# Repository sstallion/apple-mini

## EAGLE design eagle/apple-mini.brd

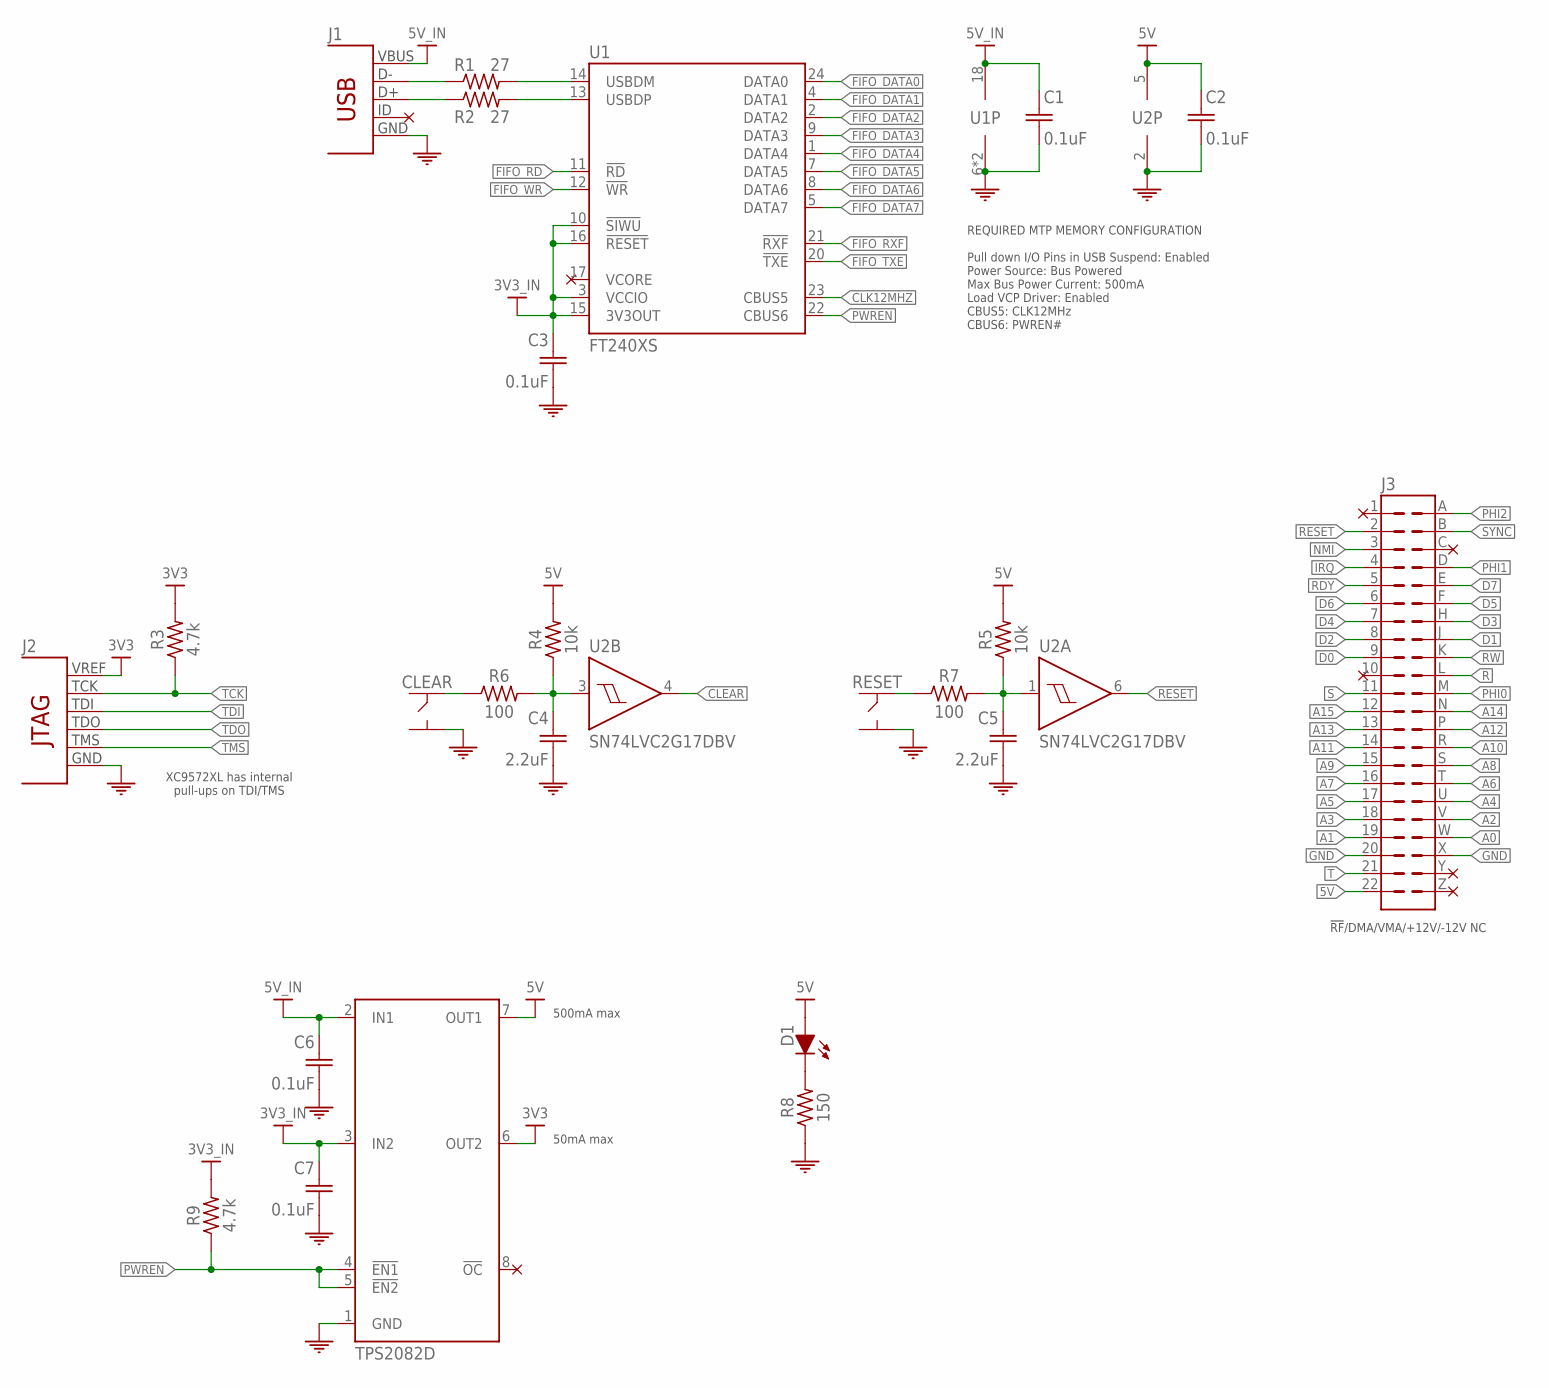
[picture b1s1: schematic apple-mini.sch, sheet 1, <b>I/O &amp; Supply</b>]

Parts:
C1, C2, C3, C6, C7: 0.1uF; 0603; MFR_PARTNO C0603C104K4RACTU
C4, C5: 2.2uF; 0603; MFR_PARTNO C0603C225K4PACTU
CLEAR: TACTSW; SMTR92
D1: CHIPLED; 0603; MFR_PARTNO LTST-C190KGKT
J1: USBMICRO; 10118193-0001LF
J2: JTAG; PH07-2-SMT
J3: RBM22DRTN; M22DRTN
R1, R2: 27; 0402; MFR_PARTNO RC0402JR-0727RL
R3, R9: 4.7k; 0603; MFR_PARTNO RC0603JR-074K7L
R4, R5: 10k; 0603; MFR_PARTNO RC0603JR-0710KL
R6, R7: 100; 0603; MFR_PARTNO ESR03EZPJ101
R8: 150; 0603; MFR_PARTNO ESR03EZPJ181
RESET: TACTSW; SMTR92
U1: FT240XS; SSOP24
U2: SN74LVC2G17DBV; SOT23-6
U3: TPS2082D; SOIC8

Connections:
3V3: J2.2 (VREF), R3.2, U3.6 (OUT2); also elsewhere on the board
3V3_IN: C3.1, C7.1, R9.2, U1.3 (VCCIO), U1.10 (!SIWU), U1.15 (3V3OUT), U1.16 (!RESET), U3.3 (IN2)
5V: C2.1, D1.2, J3.22, R4.2, R5.2, U2.5 (VCC), U3.7 (OUT1); also elsewhere on the board
5V_IN: C1.1, C6.1, J1.1, U1.18 (VCC), U3.2 (IN1)
A0: J3.W; also elsewhere on the board
A1: J3.19; also elsewhere on the board
A2: J3.V; also elsewhere on the board
A3: J3.18; also elsewhere on the board
A4: J3.U; also elsewhere on the board
A5: J3.17; also elsewhere on the board
A6: J3.T; also elsewhere on the board
A7: J3.16; also elsewhere on the board
A8: J3.S; also elsewhere on the board
A9: J3.15; also elsewhere on the board
A10: J3.R; also elsewhere on the board
A11: J3.14; also elsewhere on the board
A12: J3.P; also elsewhere on the board
A13: J3.13; also elsewhere on the board
A14: J3.N; also elsewhere on the board
A15: J3.12; also elsewhere on the board
CLEAR: U2.4 (Y); also elsewhere on the board
CLK12MHZ: U1.23 (CBUS5); also elsewhere on the board
D0: J3.9; also elsewhere on the board
D1: J3.J; also elsewhere on the board
D2: J3.8; also elsewhere on the board
D3: J3.H; also elsewhere on the board
D4: J3.7; also elsewhere on the board
D5: J3.F; also elsewhere on the board
D6: J3.6; also elsewhere on the board
D7: J3.E; also elsewhere on the board
FIFO_DATA0: U1.24 (DATA0); also elsewhere on the board
FIFO_DATA1: U1.4 (DATA1); also elsewhere on the board
FIFO_DATA2: U1.2 (DATA2); also elsewhere on the board
FIFO_DATA3: U1.9 (DATA3); also elsewhere on the board
FIFO_DATA4: U1.1 (DATA4); also elsewhere on the board
FIFO_DATA5: U1.7 (DATA5); also elsewhere on the board
FIFO_DATA6: U1.8 (DATA6); also elsewhere on the board
FIFO_DATA7: U1.5 (DATA7); also elsewhere on the board
FIFO_RD: U1.11 (!RD); also elsewhere on the board
FIFO_RXF: U1.21 (!RXF); also elsewhere on the board
FIFO_TXE: U1.20 (!TXE); also elsewhere on the board
FIFO_WR: U1.12 (!WR); also elsewhere on the board
GND: C1.2, C2.2, C3.2, C4.2, C5.2, C6.2, C7.2, CLEAR.3 (2), CLEAR.4 (2), J1.5, J1.6 (5), J1.7 (5), J1.8 (5), J1.9 (5), J2.3 (GND), J2.5 (GND), J2.7 (GND), J2.9 (GND), J2.11 (GND), J3.20, J3.X, R8.1, RESET.3 (2), RESET.4 (2), U1.6 (GND), U1.19 (GND), U2.2 (GND), U3.1 (GND); also elsewhere on the board
IRQ: J3.4; also elsewhere on the board
unnamed: D1.1, R8.2
unnamed: J1.2, R1.1
unnamed: J1.3, R2.1
unnamed: CLEAR.1, CLEAR.2 (1), R6.1
unnamed: R1.2, U1.14 (USBDM)
unnamed: R2.2, U1.13 (USBDP)
unnamed: R7.1, RESET.1, RESET.2 (1)
unnamed: C4.1, R4.1, R6.2, U2.3 (A)
unnamed: C5.1, R5.1, R7.2, U2.1 (A)
NMI: J3.3; also elsewhere on the board
PHI0: J3.M; also elsewhere on the board
PHI1: J3.D; also elsewhere on the board
PHI2: J3.A; also elsewhere on the board
PWREN: R9.1, U1.22 (CBUS6), U3.4 (!EN1), U3.5 (!EN2)
R: J3.L; also elsewhere on the board
RDY: J3.5; also elsewhere on the board
RESET: J3.2, U2.6 (Y); also elsewhere on the board
RW: J3.K; also elsewhere on the board
S: J3.11; also elsewhere on the board
SYNC: J3.B; also elsewhere on the board
T: J3.21; also elsewhere on the board
TCK: J2.6 (TCK), R3.1; also elsewhere on the board
TDI: J2.10 (TDI); also elsewhere on the board
TDO: J2.8 (TDO); also elsewhere on the board
TMS: J2.4 (TMS); also elsewhere on the board
VCORE: U1.17 (VCORE)

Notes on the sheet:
XC9572XL has internal pull-ups on TDI/TMS
!RF!/DMA/VMA/+12V/-12V NC
REQUIRED MTP MEMORY CONFIGURATION Pull down I/O Pins in USB Suspend: Enabled Power Source: Bus Powered Max Bus Power Current: 500mA Load VCP Driver: Enabled CBUS5: CLK12MHz CBUS6: PWREN#
50mA max
500mA max

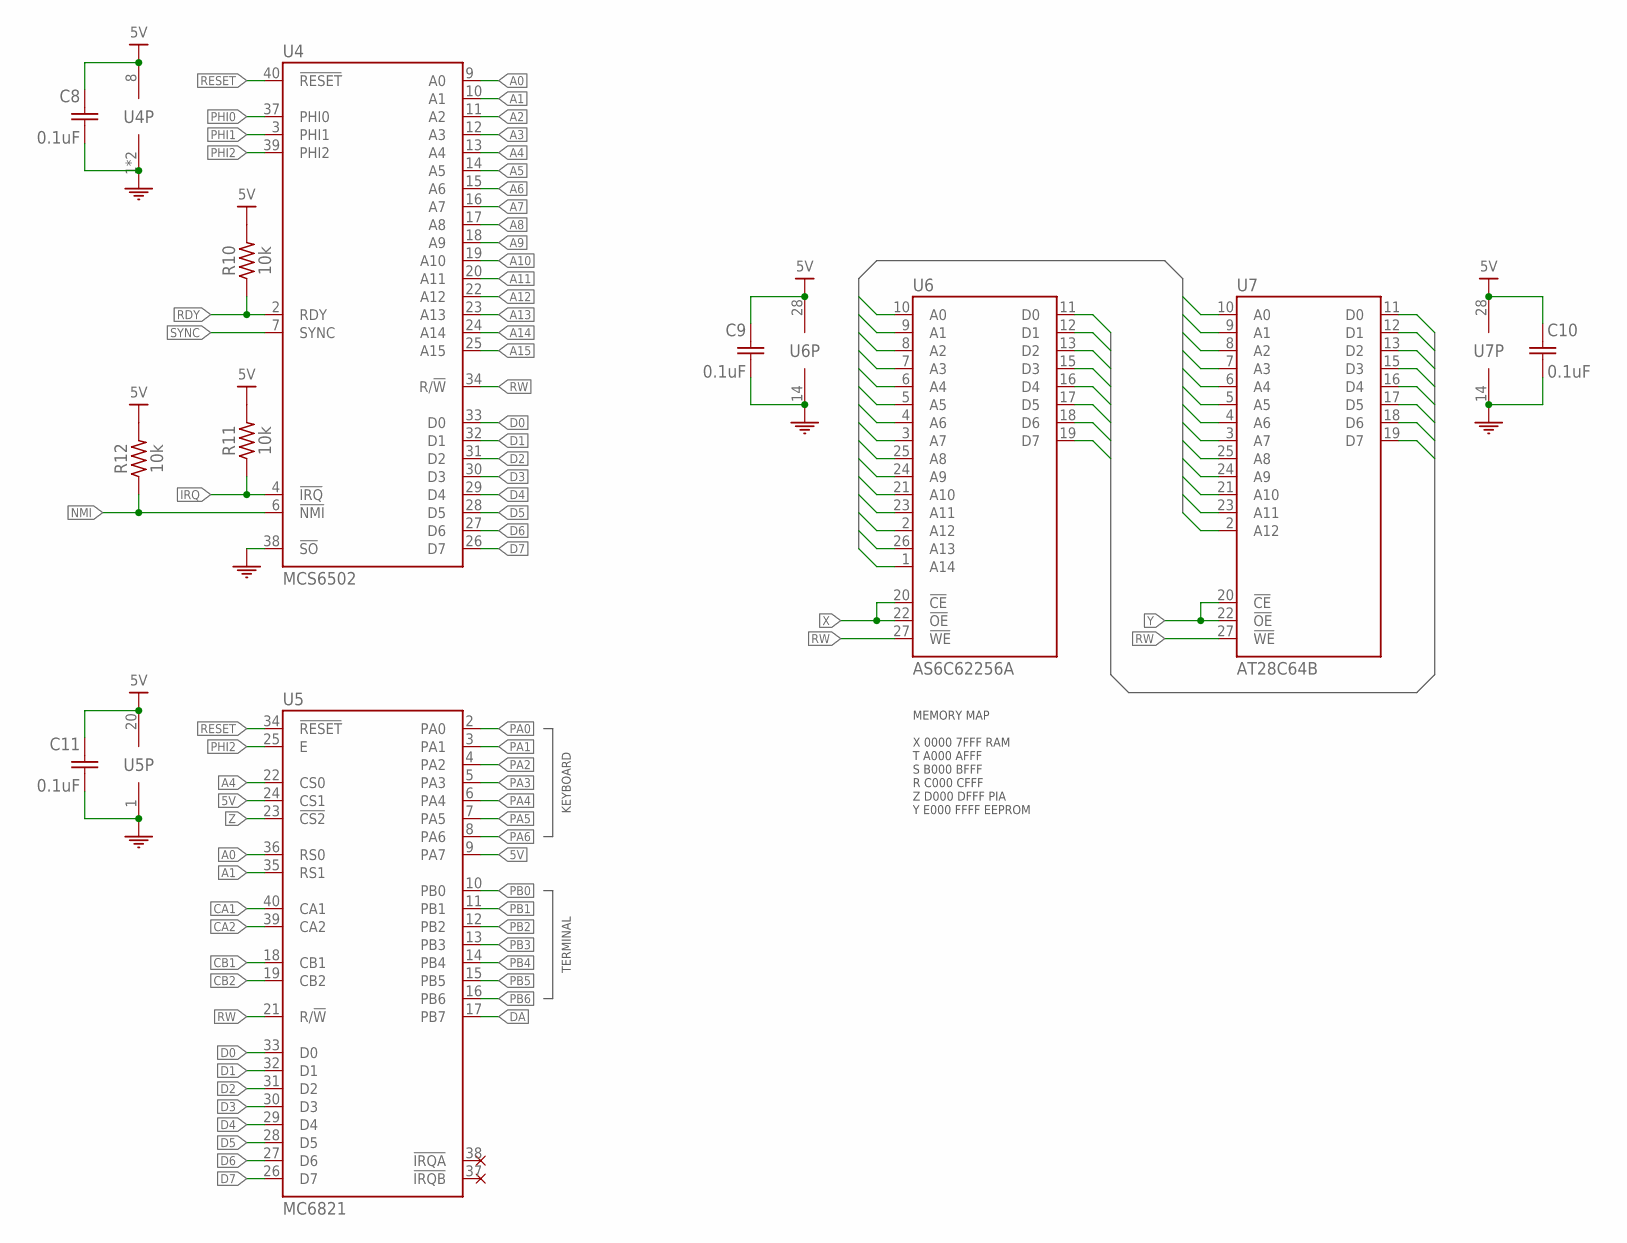
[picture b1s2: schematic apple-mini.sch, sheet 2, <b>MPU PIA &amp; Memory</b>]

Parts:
C8, C9, C10, C11: 0.1uF; 0603; MFR_PARTNO C0603C104K4RACTU
R10, R11, R12: 10k; 0603; MFR_PARTNO RC0603JR-0710KL
U4: MCS6502; DIP40
U5: MC6821; DIP40
U6: AS6C62256A; DIP28
U7: AT28C64B; DIP28

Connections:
5V: C8.1, C9.1, C10.1, C11.1, R10.2, R11.2, R12.2, U4.8 (VCC), U5.9 (PA7), U5.20 (VCC), U5.24 (CS1), U6.28 (VCC), U7.28 (VCC); also elsewhere on the board
A0: U4.9 (A0), U5.36 (RS0), U6.10 (A0), U7.10 (A0); also elsewhere on the board
A1: U4.10 (A1), U5.35 (RS1), U6.9 (A1), U7.9 (A1); also elsewhere on the board
A2: U4.11 (A2), U6.8 (A2), U7.8 (A2); also elsewhere on the board
A3: U4.12 (A3), U6.7 (A3), U7.7 (A3); also elsewhere on the board
A4: U4.13 (A4), U5.22 (CS0), U6.6 (A4), U7.6 (A4); also elsewhere on the board
A5: U4.14 (A5), U6.5 (A5), U7.5 (A5); also elsewhere on the board
A6: U4.15 (A6), U6.4 (A6), U7.4 (A6); also elsewhere on the board
A7: U4.16 (A7), U6.3 (A7), U7.3 (A7); also elsewhere on the board
A8: U4.17 (A8), U6.25 (A8), U7.25 (A8); also elsewhere on the board
A9: U4.18 (A9), U6.24 (A9), U7.24 (A9); also elsewhere on the board
A10: U4.19 (A10), U6.21 (A10), U7.21 (A10); also elsewhere on the board
A11: U4.20 (A11), U6.23 (A11), U7.23 (A11); also elsewhere on the board
A12: U4.22 (A12), U6.2 (A12), U7.2 (A12); also elsewhere on the board
A13: U4.23 (A13), U6.26 (A13); also elsewhere on the board
A14: U4.24 (A14), U6.1 (A14); also elsewhere on the board
A15: U4.25 (A15); also elsewhere on the board
CA1: U5.40 (CA1); also elsewhere on the board
CA2: U5.39 (CA2); also elsewhere on the board
CB1: U5.18 (CB1); also elsewhere on the board
CB2: U5.19 (CB2); also elsewhere on the board
D0: U4.33 (D0), U5.33 (D0), U6.11 (D0), U7.11 (D0); also elsewhere on the board
D1: U4.32 (D1), U5.32 (D1), U6.12 (D1), U7.12 (D1); also elsewhere on the board
D2: U4.31 (D2), U5.31 (D2), U6.13 (D2), U7.13 (D2); also elsewhere on the board
D3: U4.30 (D3), U5.30 (D3), U6.15 (D3), U7.15 (D3); also elsewhere on the board
D4: U4.29 (D4), U5.29 (D4), U6.16 (D4), U7.16 (D4); also elsewhere on the board
D5: U4.28 (D5), U5.28 (D5), U6.17 (D5), U7.17 (D5); also elsewhere on the board
D6: U4.27 (D6), U5.27 (D6), U6.18 (D6), U7.18 (D6); also elsewhere on the board
D7: U4.26 (D7), U5.26 (D7), U6.19 (D7), U7.19 (D7); also elsewhere on the board
DA: U5.17 (PB7); also elsewhere on the board
GND: C8.2, C9.2, C10.2, C11.2, U4.1 (GND), U4.21 (GND), U4.38 (!SO), U5.1 (GND), U6.14 (GND), U7.14 (GND); also elsewhere on the board
IRQ: R11.1, U4.4 (!IRQ); also elsewhere on the board
NMI: R12.1, U4.6 (!NMI); also elsewhere on the board
PA0: U5.2 (PA0); also elsewhere on the board
PA1: U5.3 (PA1); also elsewhere on the board
PA2: U5.4 (PA2); also elsewhere on the board
PA3: U5.5 (PA3); also elsewhere on the board
PA4: U5.6 (PA4); also elsewhere on the board
PA5: U5.7 (PA5); also elsewhere on the board
PA6: U5.8 (PA6); also elsewhere on the board
PB0: U5.10 (PB0); also elsewhere on the board
PB1: U5.11 (PB1); also elsewhere on the board
PB2: U5.12 (PB2); also elsewhere on the board
PB3: U5.13 (PB3); also elsewhere on the board
PB4: U5.14 (PB4); also elsewhere on the board
PB5: U5.15 (PB5); also elsewhere on the board
PB6: U5.16 (PB6); also elsewhere on the board
PHI0: U4.37 (PHI0); also elsewhere on the board
PHI1: U4.3 (PHI1); also elsewhere on the board
PHI2: U4.39 (PHI2), U5.25 (E); also elsewhere on the board
RDY: R10.1, U4.2 (RDY); also elsewhere on the board
RESET: U4.40 (!RESET), U5.34 (!RESET); also elsewhere on the board
RW: U4.34 (R/!W), U5.21 (R/!W), U6.27 (!WE), U7.27 (!WE); also elsewhere on the board
SYNC: U4.7 (SYNC); also elsewhere on the board
X: U6.20 (!CE), U6.22 (!OE); also elsewhere on the board
Y: U7.20 (!CE), U7.22 (!OE); also elsewhere on the board
Z: U5.23 (!CS2); also elsewhere on the board

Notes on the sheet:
MEMORY MAP X 0000 7FFF RAM T A000 AFFF S B000 BFFF R C000 CFFF Z D000 DFFF PIA Y E000 FFFF EEPROM
KEYBOARD
TERMINAL

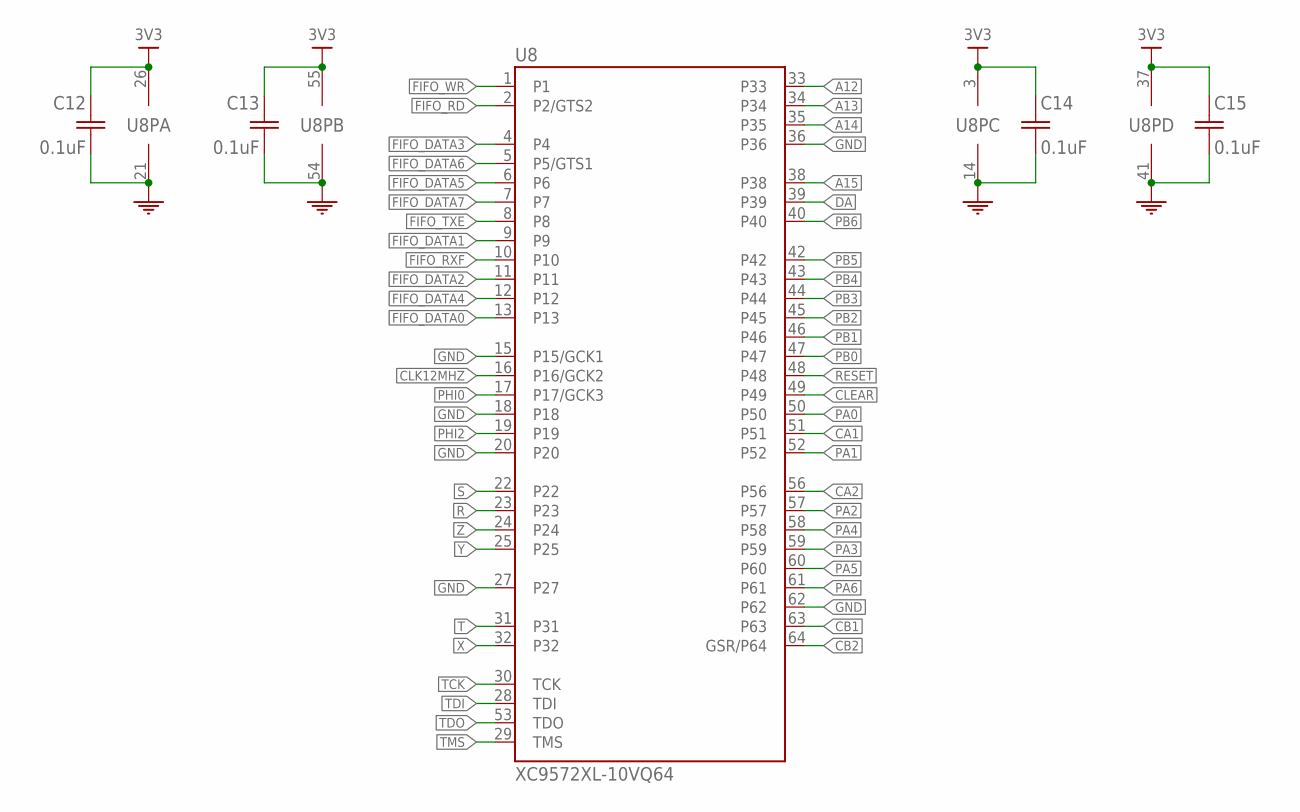
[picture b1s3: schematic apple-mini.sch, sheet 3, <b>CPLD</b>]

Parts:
C12, C13, C14, C15: 0.1uF; 0603; MFR_PARTNO C0603C104K4RACTU
U8: XC9572XL-10VQ64; VQFP64

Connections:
3V3: C12.1, C13.1, C14.1, C15.1, U8.3 (VCC), U8.26 (VCC), U8.37 (VCC), U8.55 (VCC); also elsewhere on the board
A12: U8.33; also elsewhere on the board
A13: U8.34; also elsewhere on the board
A14: U8.35; also elsewhere on the board
A15: U8.38; also elsewhere on the board
CA1: U8.51; also elsewhere on the board
CA2: U8.56; also elsewhere on the board
CB1: U8.63; also elsewhere on the board
CB2: U8.64 (GSR/P64); also elsewhere on the board
CLEAR: U8.49; also elsewhere on the board
CLK12MHZ: U8.16 (P16/GCK2); also elsewhere on the board
DA: U8.39; also elsewhere on the board
FIFO_DATA0: U8.13; also elsewhere on the board
FIFO_DATA1: U8.9; also elsewhere on the board
FIFO_DATA2: U8.11; also elsewhere on the board
FIFO_DATA3: U8.4; also elsewhere on the board
FIFO_DATA4: U8.12; also elsewhere on the board
FIFO_DATA5: U8.6; also elsewhere on the board
FIFO_DATA6: U8.5 (P5/GTS1); also elsewhere on the board
FIFO_DATA7: U8.7; also elsewhere on the board
FIFO_RD: U8.2 (P2/GTS2); also elsewhere on the board
FIFO_RXF: U8.10; also elsewhere on the board
FIFO_TXE: U8.8; also elsewhere on the board
FIFO_WR: U8.1; also elsewhere on the board
GND: C12.2, C13.2, C14.2, C15.2, U8.14 (GND), U8.15 (P15/GCK1), U8.18, U8.20, U8.21 (GND), U8.27, U8.36, U8.41 (GND), U8.54 (GND), U8.62; also elsewhere on the board
PA0: U8.50; also elsewhere on the board
PA1: U8.52; also elsewhere on the board
PA2: U8.57; also elsewhere on the board
PA3: U8.59; also elsewhere on the board
PA4: U8.58; also elsewhere on the board
PA5: U8.60; also elsewhere on the board
PA6: U8.61; also elsewhere on the board
PB0: U8.47; also elsewhere on the board
PB1: U8.46; also elsewhere on the board
PB2: U8.45; also elsewhere on the board
PB3: U8.44; also elsewhere on the board
PB4: U8.43; also elsewhere on the board
PB5: U8.42; also elsewhere on the board
PB6: U8.40; also elsewhere on the board
PHI0: U8.17 (P17/GCK3); also elsewhere on the board
PHI2: U8.19; also elsewhere on the board
R: U8.23; also elsewhere on the board
RESET: U8.48; also elsewhere on the board
S: U8.22; also elsewhere on the board
T: U8.31; also elsewhere on the board
TCK: U8.30 (TCK); also elsewhere on the board
TDI: U8.28 (TDI); also elsewhere on the board
TDO: U8.53 (TDO); also elsewhere on the board
TMS: U8.29 (TMS); also elsewhere on the board
X: U8.32; also elsewhere on the board
Y: U8.25; also elsewhere on the board
Z: U8.24; also elsewhere on the board

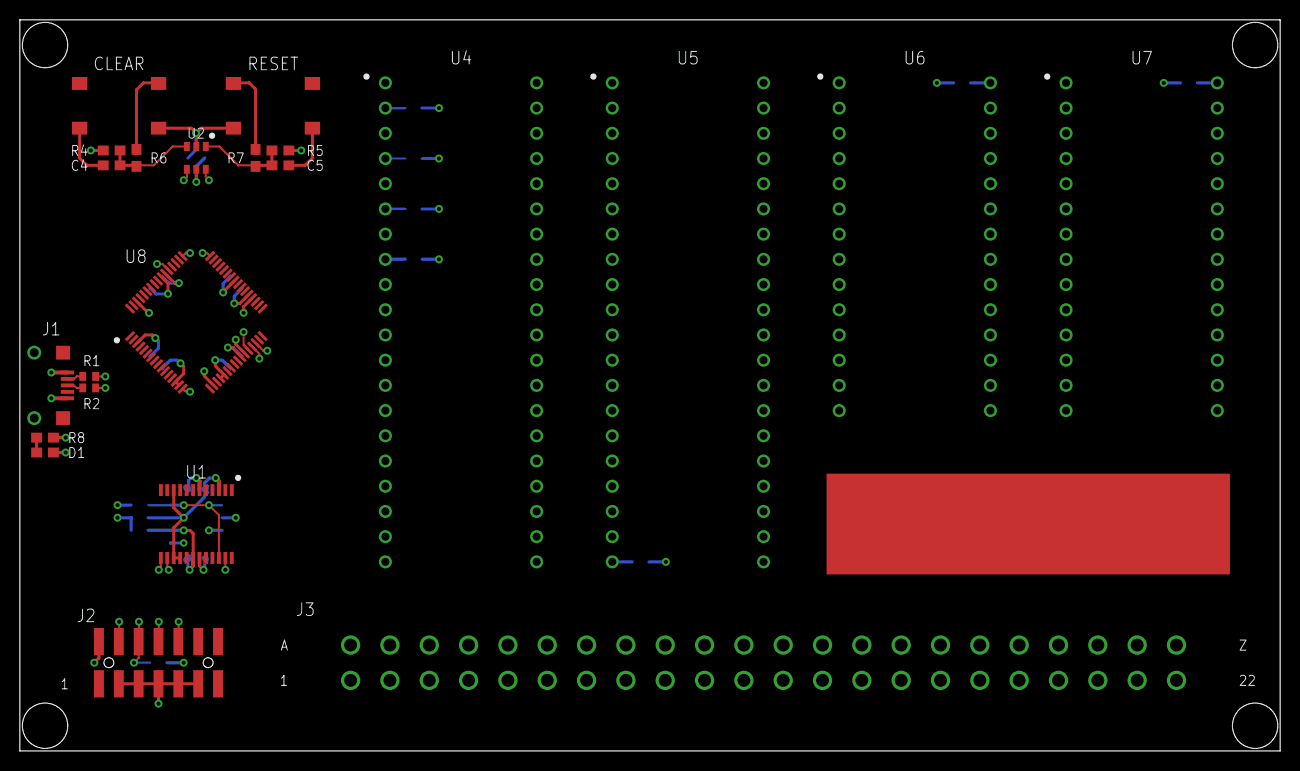
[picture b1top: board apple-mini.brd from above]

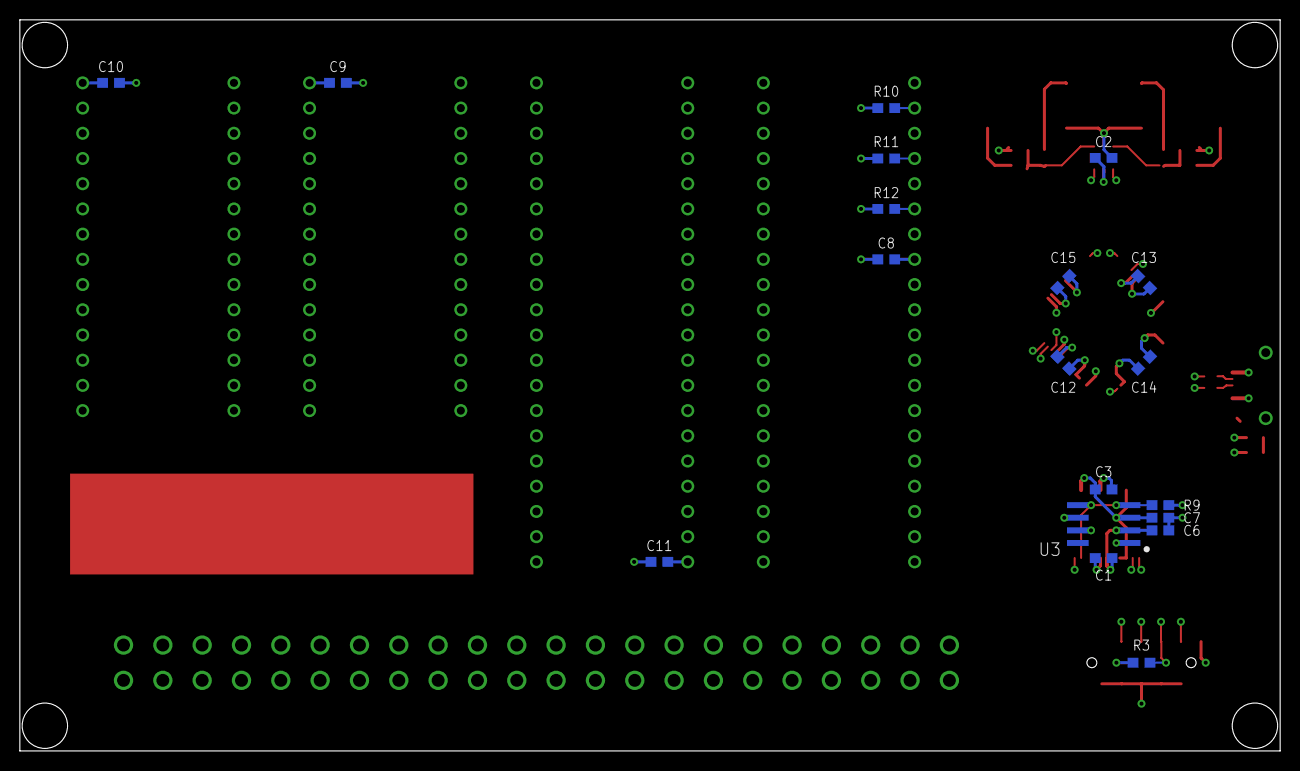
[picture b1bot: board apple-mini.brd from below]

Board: 4 copper layers, 127.0 x 73.7 mm, 41 parts (19 on the bottom side), 91 nets.

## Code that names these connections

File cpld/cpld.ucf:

# Copyright (c) 2015 Steven Stallion
# All rights reserved.
#
# Redistribution and use in source and binary forms, with or without
# modification, are permitted provided that the following conditions
# are met:
# 1. Redistributions of source code must retain the above copyright
#    notice, this list of conditions and the following disclaimer.
# 2. Redistributions in binary form must reproduce the above copyright
#    notice, this list of conditions and the following disclaimer in the
#    documentation and/or other materials provided with the distribution.
#
# THIS SOFTWARE IS PROVIDED BY THE AUTHOR AND CONTRIBUTORS ``AS IS'' AND
# ANY EXPRESS OR IMPLIED WARRANTIES, INCLUDING, BUT NOT LIMITED TO, THE
# IMPLIED WARRANTIES OF MERCHANTABILITY AND FITNESS FOR A PARTICULAR PURPOSE
# ARE DISCLAIMED.  IN NO EVENT SHALL THE AUTHOR OR CONTRIBUTORS BE LIABLE
# FOR ANY DIRECT, INDIRECT, INCIDENTAL, SPECIAL, EXEMPLARY, OR CONSEQUENTIAL
# DAMAGES (INCLUDING, BUT NOT LIMITED TO, PROCUREMENT OF SUBSTITUTE GOODS
# OR SERVICES; LOSS OF USE, DATA, OR PROFITS; OR BUSINESS INTERRUPTION)
# HOWEVER CAUSED AND ON ANY THEORY OF LIABILITY, WHETHER IN CONTRACT, STRICT
# LIABILITY, OR TORT (INCLUDING NEGLIGENCE OR OTHERWISE) ARISING IN ANY WAY
# OUT OF THE USE OF THIS SOFTWARE, EVEN IF ADVISED OF THE POSSIBILITY OF
# SUCH DAMAGE.

NET "reset" LOC = "P48";
NET "clear" LOC = "P49";

# clk_div
NET "clk_in" LOC = "P16" | BUFG = CLK;
NET "clk_out" LOC = "P17";

# addr_decode
NET "addr<0>" LOC = "P33";
NET "addr<1>" LOC = "P34";
NET "addr<2>" LOC = "P35";
NET "addr<3>" LOC = "P36";
NET "r" LOC = "P19";
NET "s" LOC = "P20";
NET "t" LOC = "P22";
NET "x" LOC = "P23";
NET "y" LOC = "P24";
NET "z" LOC = "P25";

# fifo_mux
NET "pia_e" LOC = "P32";
NET "pia_ca1" LOC = "P61";
NET "pia_ca2" LOC = "P62";
NET "pia_cb1" LOC = "P63";
NET "pia_cb2" LOC = "P64";
NET "pia_pa<0>" LOC = "P51";
NET "pia_pa<1>" LOC = "P52";
NET "pia_pa<2>" LOC = "P56";
NET "pia_pa<3>" LOC = "P57";
NET "pia_pa<4>" LOC = "P58";
NET "pia_pa<5>" LOC = "P59";
NET "pia_pa<6>" LOC = "P60";
NET "pia_pb<0>" LOC = "P39";
NET "pia_pb<1>" LOC = "P40";
NET "pia_pb<2>" LOC = "P42";
NET "pia_pb<3>" LOC = "P43";
NET "pia_pb<4>" LOC = "P44";
NET "pia_pb<5>" LOC = "P45";
NET "pia_pb<6>" LOC = "P46";
NET "pia_da" LOC = "P47";
NET "fifo_rxf" LOC = "P12";
NET "fifo_txe" LOC = "P13";
NET "fifo_rd" LOC = "P10";
NET "fifo_wr" LOC = "P11";
NET "fifo_data<0>" LOC = "P1";
NET "fifo_data<1>" LOC = "P2";
NET "fifo_data<2>" LOC = "P4";
NET "fifo_data<3>" LOC = "P5";
NET "fifo_data<4>" LOC = "P6";
NET "fifo_data<5>" LOC = "P7";
NET "fifo_data<6>" LOC = "P8";
NET "fifo_data<7>" LOC = "P9";

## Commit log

2015-07-10 Add multiple sheets; finalize FIFO and load switch
2015-07-10 Switch to synchronous CPLD design
2015-07-15 Cleanup; add PoR and JTAG
2015-07-15 Invert pia_cb2 input in pia_da assignment
2015-07-17 Rename project; sundry style updates
2015-07-17 Add remaining footprints
2015-07-19 Add CPLD and clear switch
2015-07-20 Add schmitt buffer on clear/reset
2015-07-21 Add MPU and PIA to schematic
2015-07-26 Finalize schematic; initial board placement
2015-07-27 Add DRC rules and logo bitmap to board layout
2015-07-28 Generate BOM
2015-08-06 Route critical signals
2015-08-23 Route power and remaining critical nets
2015-09-26 Initial (and incomplete) gerbers
2018-10-13 Update LICENSE

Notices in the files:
parts and their libraries:
apple-mini: BY A BSD-STYLE LICENSE THAT CAN
